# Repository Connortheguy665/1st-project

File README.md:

# 1st-project

What it is
its basically a tiny electronic toy that you can use and have a pet 

Why?
this was the week 1 half life project and it was an opportunity to explore the world of creation

Project status
The PCB was completed and submitted to the team in order to get it fabricated

Software
for this device i used arduino in order to be able to code this

Controls: you can use the buttons on the starbie to control and select certain things on it 
 here is my BOM
 https://github.com/Connortheguy665/1st-project/blob/main/BOM.csv

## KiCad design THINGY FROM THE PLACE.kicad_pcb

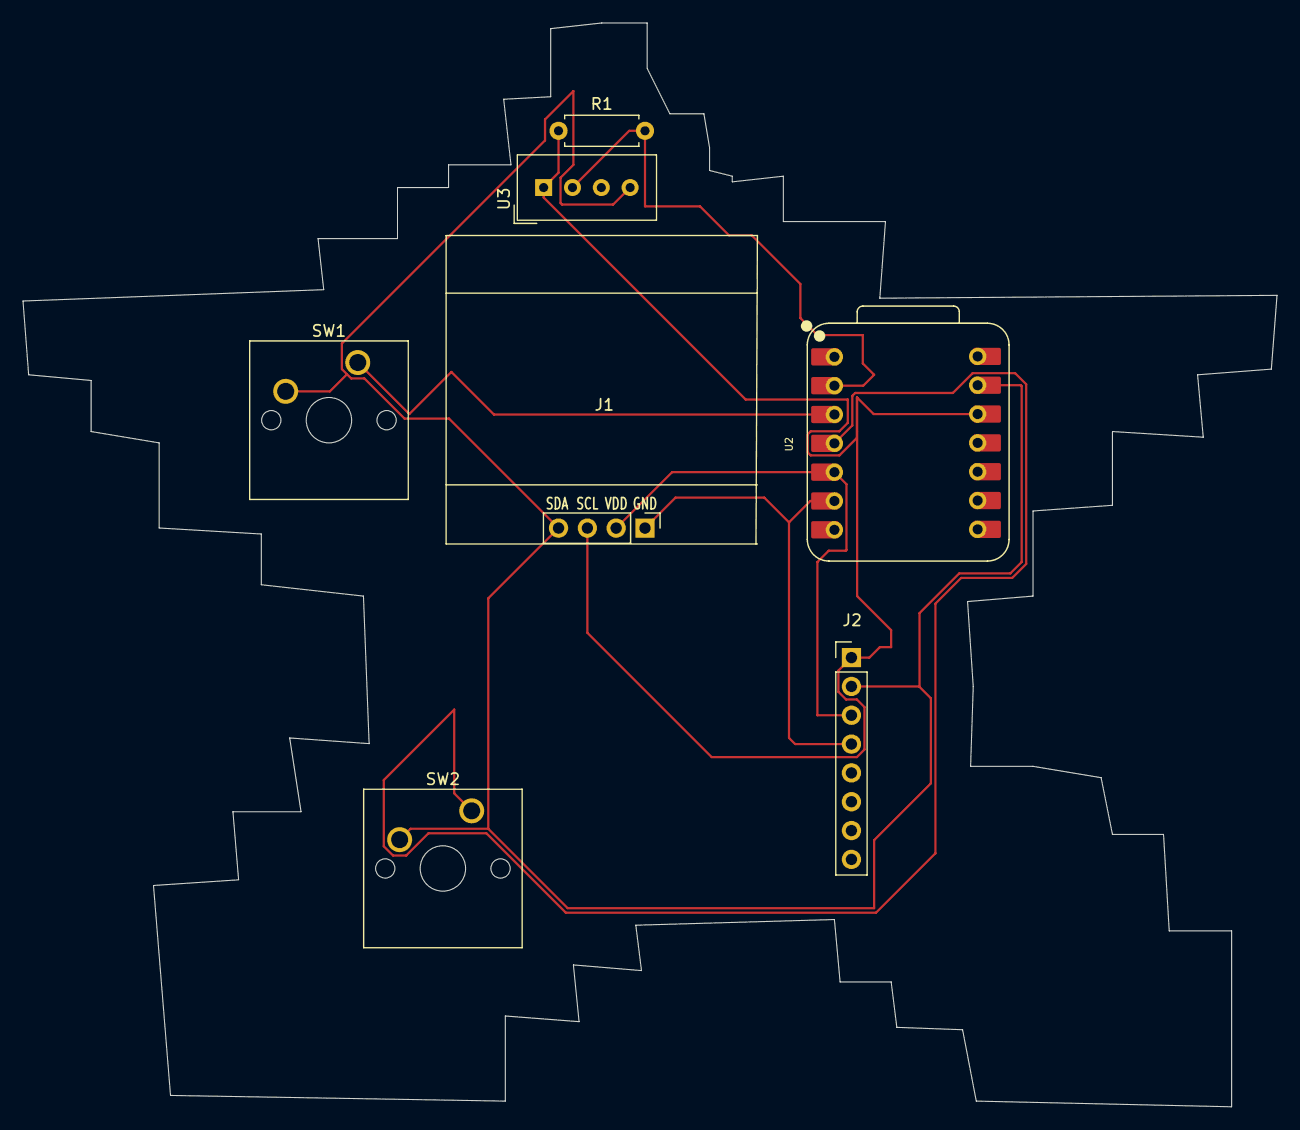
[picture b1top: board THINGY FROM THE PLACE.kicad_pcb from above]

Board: 2 copper layers, 110.5 x 95.5 mm, 7 parts (0 on the bottom side), 7 nets.

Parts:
J1: Conn_01x04_Pin; Display_128x64_096_I2C
J2: Conn_01x08_Pin; PinHeader_1x08_P2.54mm_Vertical
R1: 10k; R_Axial_DIN0207_L6.3mm_D2.5mm_P7.62mm_Horizontal
SW1, SW2: SW_Push; SW_Cherry_MX_1.00u_PCB
U2: XIAO-ESP32-C3-SMD; XIAO-ESP32-C6-DIP
U3: DHT11; Aosong_DHT11_5.5x12.0_P2.54mm

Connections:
+3.3V: J1.3, J2.1, R1.1, U2.12 (3V3_OUT), U3.1 (VDD)
/DHT11 DATA: R1.2, U2.2 (D1), U3.2 (DATA)
/GPIO2: SW1.1, U2.3 (D2)
/GPIO3: SW2.1, U2.4 (D3)
/SCL: J1.2, J2.3, U2.5 (D4)
/SDA: J1.1, J2.4, U2.6 (D5)
GND: J1.4, J2.2, SW1.2, SW2.2, U2.13 (GND), U3.4 (GND)
